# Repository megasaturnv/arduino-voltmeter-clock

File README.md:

# arduino-voltmeter-clock
An Arduino-based clock which displays the date and time with voltmeters

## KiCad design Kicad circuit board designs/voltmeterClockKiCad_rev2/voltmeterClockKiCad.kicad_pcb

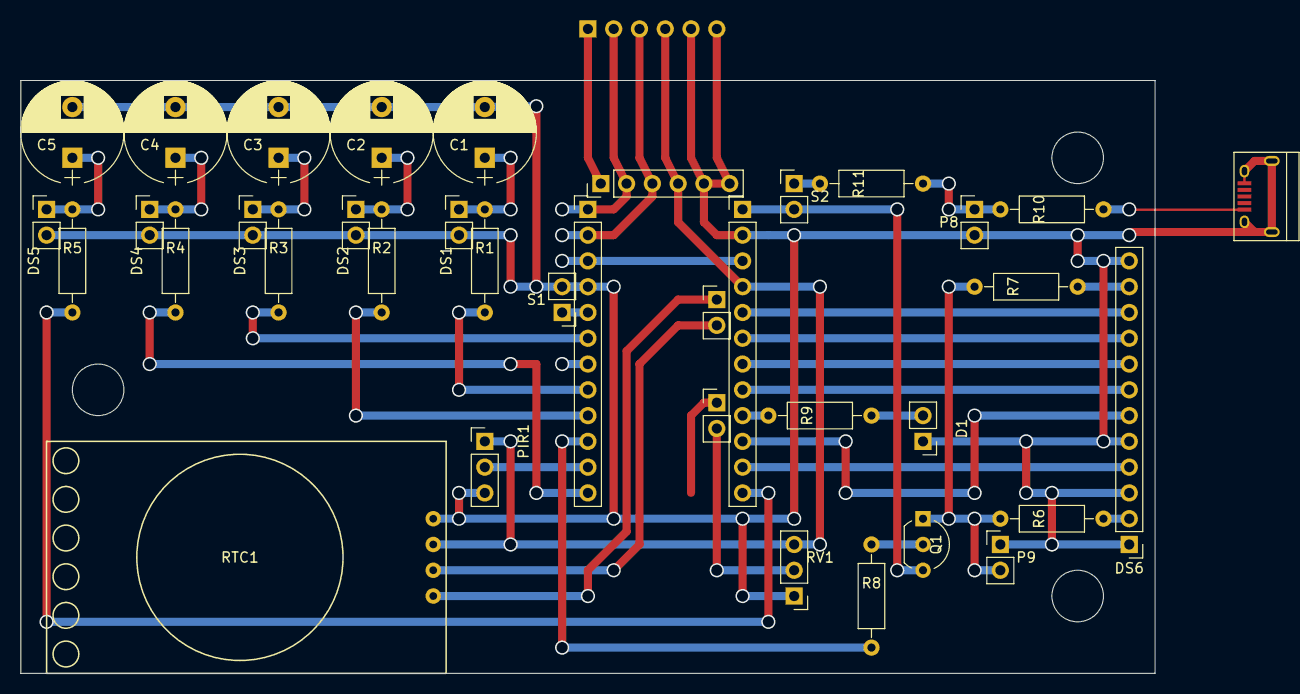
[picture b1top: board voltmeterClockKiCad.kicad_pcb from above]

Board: 2 copper layers, 111.8 x 58.4 mm, 38 parts (1 on the bottom side), 38 nets.

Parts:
C1, C2, C3, C4, C5: 47uF; CP_Radial_D10.0mm_P5.00mm
D1: LED; Pin_Header_Straight_1x02_Pitch2.54mm
DS1: VU_SECS; Pin_Header_Straight_1x02_Pitch2.54mm
DS2: VU_MINS; Pin_Header_Straight_1x02_Pitch2.54mm
DS3: VU_HOURS; Pin_Header_Straight_1x02_Pitch2.54mm
DS4: VU_DAY; Pin_Header_Straight_1x02_Pitch2.54mm
DS5: VU_MONTH; Pin_Header_Straight_1x02_Pitch2.54mm
DS6: 2004_LCD_DISPLAY; Pin_Header_Straight_1x12_Pitch2.54mm
P1: Digital; Socket_Strip_Straight_1x12_Pitch2.54mm
P2: COM; Pin_Header_Straight_1x06_Pitch2.54mm
P3, P5: ADC; Pin_Header_Straight_1x02_Pitch2.54mm
P4: Analog; Socket_Strip_Straight_1x12_Pitch2.54mm
P6: Serial_Conn; Socket_Strip_Angled_1x06_Pitch2.54mm
P7: USB_OTG; USB_Micro-B
P8: Battery_Conn; Pin_Header_Straight_1x02_Pitch2.54mm
P9: Backlight_Conn; Pin_Header_Straight_1x02_Pitch2.54mm
PIR1: PIR_SENSOR; Pin_Header_Straight_1x03_Pitch2.54mm
Q1: Q_PNP_CBE; TO-92_Inline_Wide
R1, R2, R3, R4, R5: 470R; R_Axial_DIN0207_L6.3mm_D2.5mm_P10.16mm_Horizontal
R6: 300R; R_Axial_DIN0207_L6.3mm_D2.5mm_P10.16mm_Horizontal
R7, R9: 1000R; R_Axial_DIN0207_L6.3mm_D2.5mm_P10.16mm_Horizontal
R8: 10000R; R_Axial_DIN0207_L6.3mm_D2.5mm_P10.16mm_Horizontal
R10, R11: 56R; R_Axial_DIN0207_L6.3mm_D2.5mm_P10.16mm_Horizontal
RTC1: RTC_DS3231
RV1: POT100kR; Pin_Header_Straight_1x03_Pitch2.54mm
S1: PUSH_BUTTON; Pin_Header_Straight_1x02_Pitch2.54mm
S2: ON/OFF_SWITCH; Pin_Header_Straight_1x02_Pitch2.54mm

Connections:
+3V3: P2.4, P4.4, P6.4, PIR1.1, RTC1.2, RV1.3
+5V: P7.1, R10.1
/0(Rx): P1.2, P2.3, P6.3
/1(Tx): P1.1, P2.2, P6.2
/2: P1.5, S1.1
/3(**): P1.6, R3.1
/5(**): P1.8, R1.1
/6(**): P1.9, R2.1
/7: P1.10, R8.1
/8: P1.11, PIR1.2
/9(**): P1.12, R4.1
/10(**/SS): P4.12, R5.1
/11(**/MOSI): DS6.4, P4.11
/12(MISO): DS6.6, P4.10
/13(SCK): P4.9, R9.2
/A0: DS6.11, P4.8
/A1: DS6.12, P4.7
/A2: DS6.13, P4.6
/A3: DS6.14, P4.5
/A4: P3.2, RTC1.3
/A5: P3.1, RTC1.4
/A6: P5.2, RV1.2
/DTR: P2.1, P6.1
/ONOFF_RAW: P8.1, R10.2, R11.1
/RAW: P4.1, Q1.3, S2.2
/Reset: P1.3, P4.3
GND: C1.2, C2.2, C3.2, C4.2, C5.2, D1.1, DS1.2, DS2.2, DS3.2, DS4.2, DS5.2, DS6.1, DS6.3, DS6.5, DS6.16, P1.4, P2.5, P2.6, P4.2, P6.5, P6.6, P7.5, P7.6, P8.2, P9.1, PIR1.3, RTC1.1, RV1.1, S1.2
unnamed: C1.1, DS1.1, R1.2
unnamed: C2.1, DS2.1, R2.2
unnamed: C3.1, DS3.1, R3.2
unnamed: C4.1, DS4.1, R4.2
unnamed: C5.1, DS5.1, R5.2
unnamed: D1.2, R9.1
unnamed: DS6.2, R6.2
unnamed: DS6.15, R7.2
unnamed: P9.2, Q1.1, R6.1, R7.1
unnamed: Q1.2, R8.2
unnamed: R11.2, S2.1

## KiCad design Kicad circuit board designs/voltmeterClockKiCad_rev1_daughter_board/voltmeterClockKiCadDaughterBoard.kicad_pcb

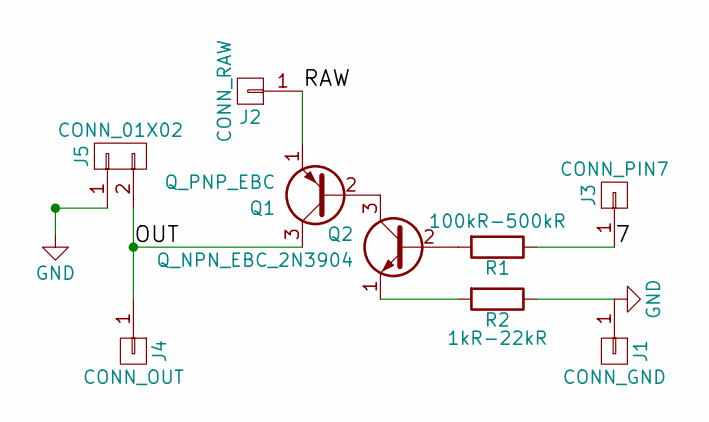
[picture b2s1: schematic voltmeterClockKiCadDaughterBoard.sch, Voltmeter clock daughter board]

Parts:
J1: CONN_GND; Pin_Header_Straight_1x01_Pitch2.54mm
J2: CONN_RAW; Pin_Header_Straight_1x01_Pitch2.54mm
J3: CONN_PIN7; Pin_Header_Straight_1x01_Pitch2.54mm
J4: CONN_OUT; Pin_Header_Straight_1x01_Pitch2.54mm
J5: CONN_01X02; Pin_Header_Straight_1x02_Pitch2.54mm
Q1: Q_PNP_EBC; TO-92_Inline_Wide
Q2: Q_NPN_EBC_2N3904; TO-92_Inline_Wide
R1: 100kR-500kR; R_Axial_DIN0207_L6.3mm_D2.5mm_P10.16mm_Horizontal
R2: 1kR-22kR; R_Axial_DIN0207_L6.3mm_D2.5mm_P10.16mm_Horizontal

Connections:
/7: J3.1, R1.1
/OUT: J4.1, J5.2, Q1.3 (C)
/RAW: J2.1, Q1.1 (E)
GND: J1.1, J5.1, R2.1
unnamed: Q1.2 (B), Q2.3 (C)
unnamed: Q2.1 (E), R2.2
unnamed: Q2.2 (B), R1.2

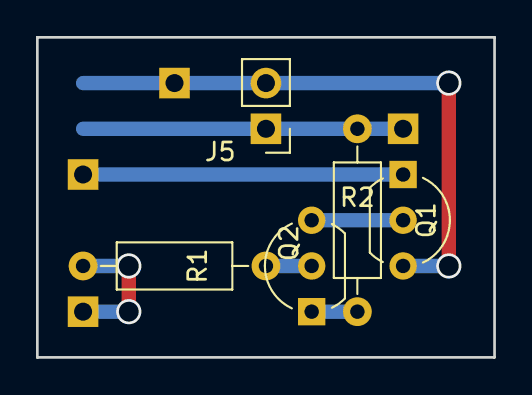
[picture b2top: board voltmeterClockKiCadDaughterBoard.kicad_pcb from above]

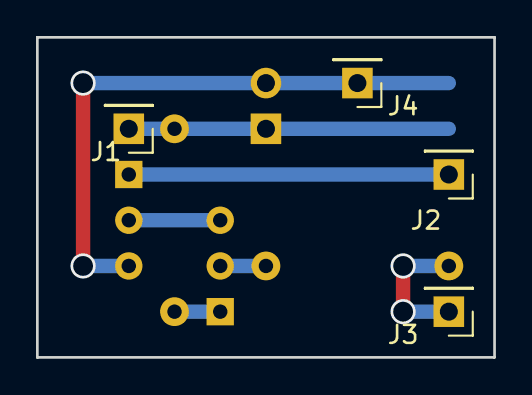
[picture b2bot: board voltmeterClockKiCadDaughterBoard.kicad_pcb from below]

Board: 2 copper layers, 25.4 x 17.8 mm, 9 parts (4 on the bottom side), 7 nets.

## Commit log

2018-02-14 Initial upload
2018-02-14 Renamed and moved files
2018-02-14 Renamed file
2018-02-14 Added PIR sensor
2018-02-14 Added Clock front layout.svg
